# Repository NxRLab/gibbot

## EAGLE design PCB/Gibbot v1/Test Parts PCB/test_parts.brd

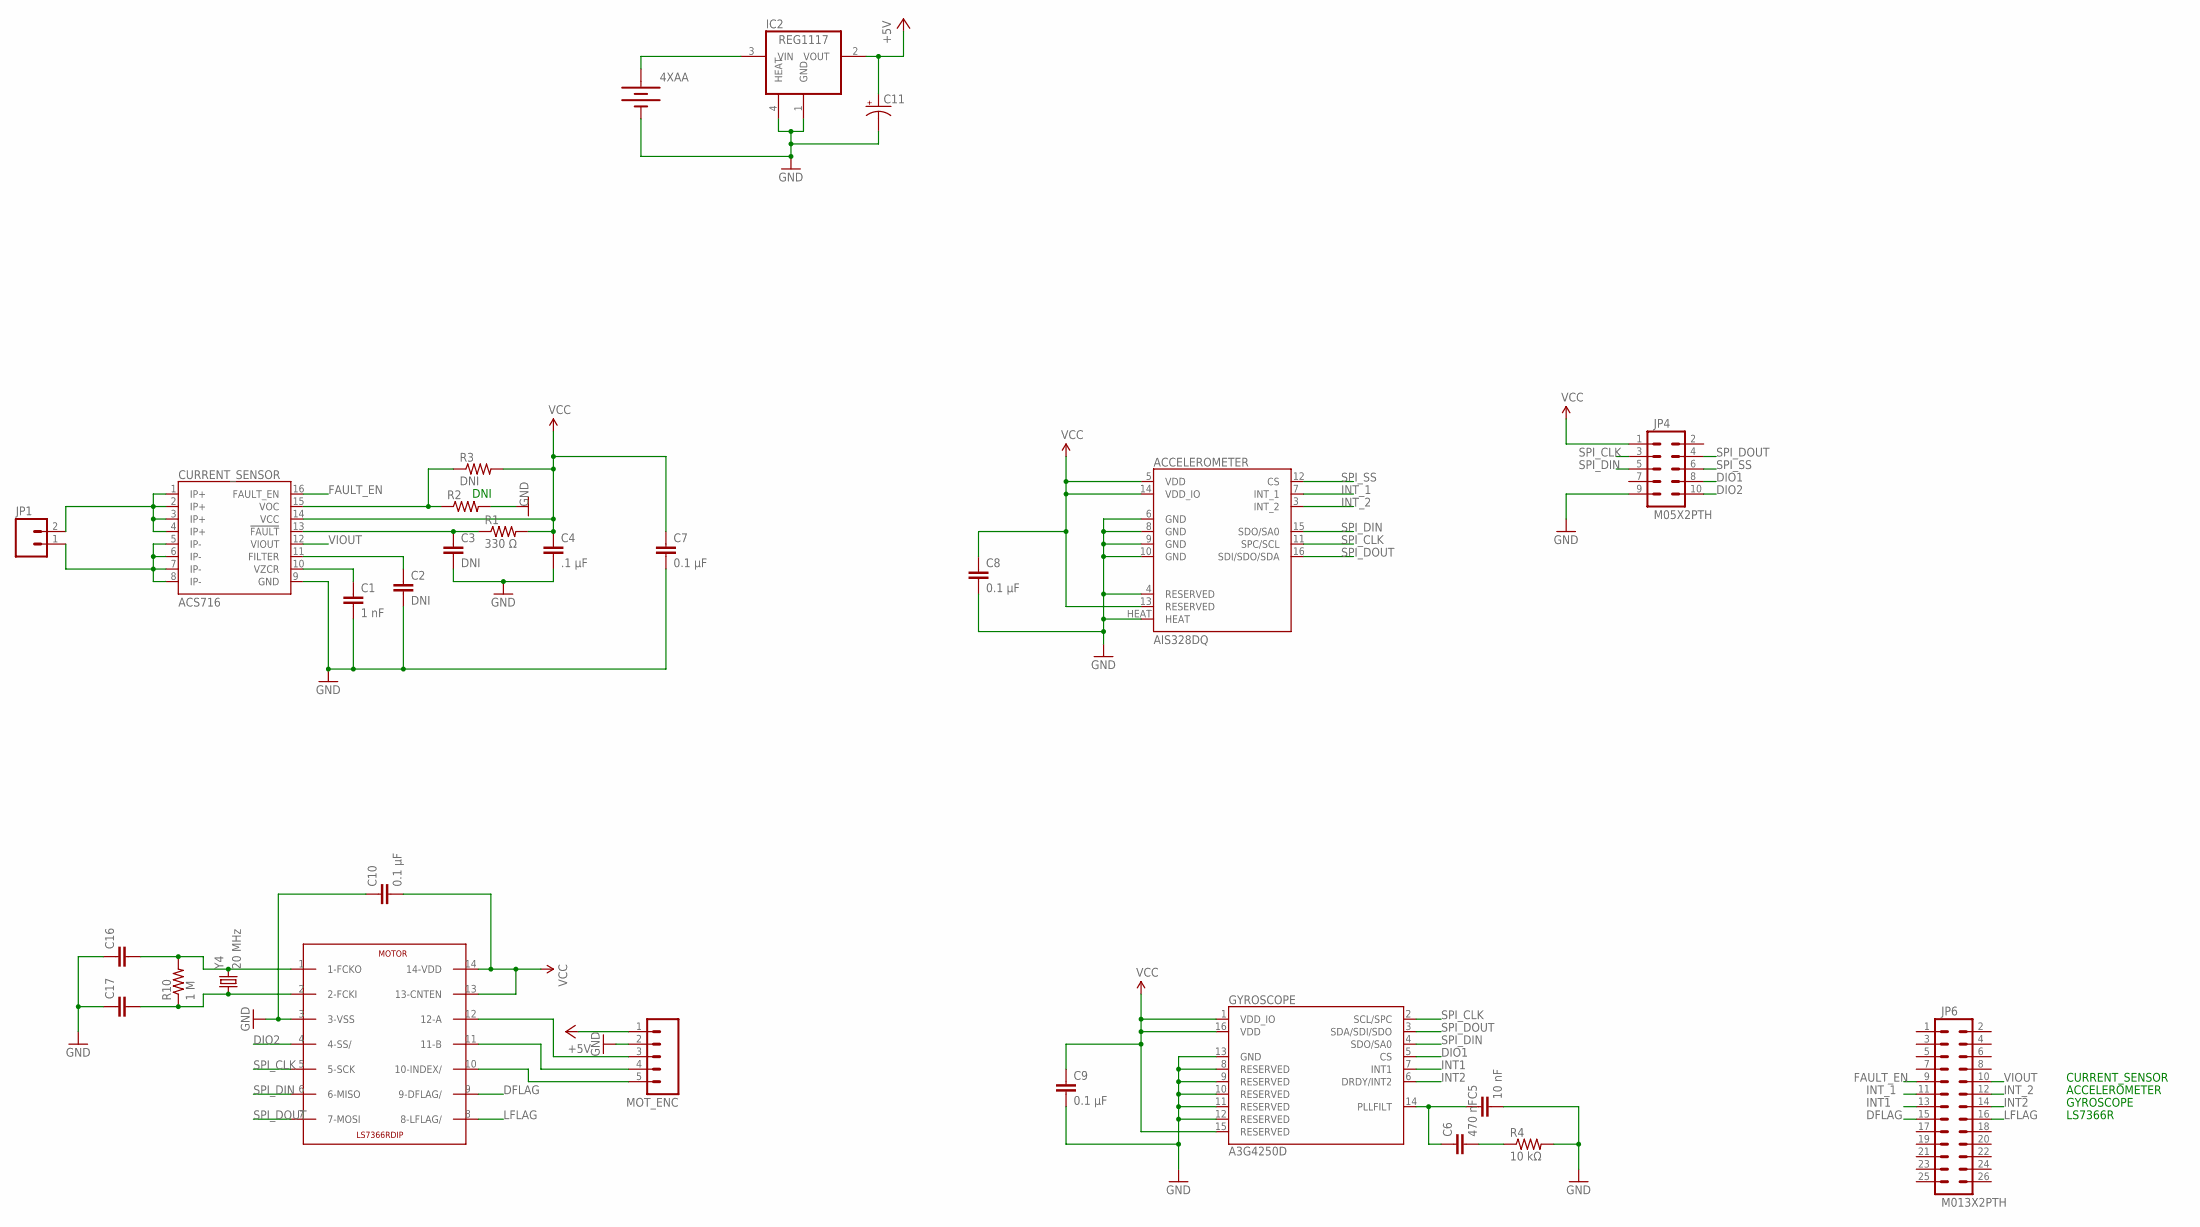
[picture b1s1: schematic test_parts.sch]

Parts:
4XAA: BATTERYTOP; BH4AA-PC
ACCELEROMETER: AIS328DQ; QFPN-24
C1: 1 nF; 0603-CAP
C2, C3: DNI; 0603-CAP
C4: .1 µF; 0603-CAP
C5: 10 nF; 0603-CAP
C6: 470 nF; 0603-CAP
C7, C8, C9, C10: 0.1 µF; 0603-CAP
C11: CAP_POL0603; 0603-CAP
C16, C17: CAP0603-CAP; 0603-CAP
CURRENT_SENSOR: ACS716; SOICW
GYROSCOPE: A3G4250D; LGA-16
IC2: REG1117; SOT223
JP1: M02PTH; 1X02
JP4: M05X2PTH; AVR_ICSP
JP6: M013X2PTH; AVR_ICSP
MOTOR: LS7366RDIP; DIL14
MOT_ENC: M05PTH; 1X05
R1: 330 Ω; 0603-RES
R2, R3: DNI; 0603-RES
R4: 10 kΩ; 0603-RES
R10: 1 M; R0603
Y4: 20 MHz; HC49US

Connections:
+5V: C11.1 (+), IC2.2 (VOUT), MOT_ENC.1
DFLAG: JP6.15, MOTOR.9 (9-DFLAG/)
DIO1: GYROSCOPE.5 (CS), JP4.8
DIO2: JP4.10, MOTOR.4 (4-SS/)
FAULT_EN: CURRENT_SENSOR.16 (FAULT_EN), JP6.9
GND: 4XAA.-, ACCELEROMETER.4 (RESERVED), ACCELEROMETER.6 (GND), ACCELEROMETER.8 (GND), ACCELEROMETER.9 (GND), ACCELEROMETER.10 (GND), ACCELEROMETER.HEAT, C1.2, C2.2, C3.2, C4.2, C5.2, C7.2, C8.2, C9.2, C10.1, C11.2 (-), C16.1, C17.1, CURRENT_SENSOR.9 (GND), GYROSCOPE.8 (RESERVED), GYROSCOPE.9 (RESERVED), GYROSCOPE.10 (RESERVED), GYROSCOPE.11 (RESERVED), GYROSCOPE.12 (RESERVED), GYROSCOPE.13 (GND), IC2.1 (GND), IC2.4 (HEAT), JP4.9, MOTOR.3 (3-VSS), MOT_ENC.2, R2.2, R4.2
INT1: GYROSCOPE.7 (INT1), JP6.13
INT2: GYROSCOPE.6 (DRDY/INT2), JP6.14
INT_1: ACCELEROMETER.7 (INT_1), JP6.11
INT_2: ACCELEROMETER.3 (INT_2), JP6.12
LFLAG: JP6.16, MOTOR.8 (8-LFLAG/)
unnamed: CURRENT_SENSOR.1 (IP+), CURRENT_SENSOR.2 (IP+), CURRENT_SENSOR.3 (IP+), CURRENT_SENSOR.4 (IP+), JP1.2
unnamed: CURRENT_SENSOR.5 (IP-), CURRENT_SENSOR.6 (IP-), CURRENT_SENSOR.7 (IP-), CURRENT_SENSOR.8 (IP-), JP1.1
unnamed: C3.1, CURRENT_SENSOR.13 (!FAULT), R1.1
unnamed: C1.1, CURRENT_SENSOR.10 (VZCR)
unnamed: C2.1, CURRENT_SENSOR.11 (FILTER)
unnamed: 4XAA.+, IC2.3 (VIN)
unnamed: CURRENT_SENSOR.15 (VOC), R2.1, R3.1
unnamed: C5.1, C6.1, GYROSCOPE.14 (PLLFILT)
unnamed: C6.2, R4.1
unnamed: C16.2, MOTOR.1 (1-FCKO), R10.2, Y4.2
unnamed: C17.2, MOTOR.2 (2-FCKI), R10.1, Y4.1
unnamed: MOTOR.12 (12-A), MOT_ENC.3
unnamed: MOTOR.11 (11-B), MOT_ENC.4
unnamed: MOTOR.10 (10-INDEX/), MOT_ENC.5
SPI_CLK: ACCELEROMETER.11 (SPC/SCL), GYROSCOPE.2 (SCL/SPC), JP4.3, MOTOR.5 (5-SCK)
SPI_DIN: ACCELEROMETER.15 (SDO/SA0), GYROSCOPE.4 (SDO/SA0), JP4.5, MOTOR.6 (6-MISO)
SPI_DOUT: ACCELEROMETER.16 (SDI/SDO/SDA), GYROSCOPE.3 (SDA/SDI/SDO), JP4.4, MOTOR.7 (7-MOSI)
SPI_SS: ACCELEROMETER.12 (CS), JP4.6
VCC: ACCELEROMETER.5 (VDD), ACCELEROMETER.13 (RESERVED), ACCELEROMETER.14 (VDD_IO), C4.1, C7.1, C8.1, C9.1, C10.2, CURRENT_SENSOR.14 (VCC), GYROSCOPE.1 (VDD_IO), GYROSCOPE.15 (RESERVED), GYROSCOPE.16 (VDD), JP4.1, MOTOR.13 (13-CNTEN), MOTOR.14 (14-VDD), R1.2, R3.2
VIOUT: CURRENT_SENSOR.12 (VIOUT), JP6.10

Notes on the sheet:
CURRENT_SENSOR
ACCELEROMETER
GYROSCOPE
LS7366R

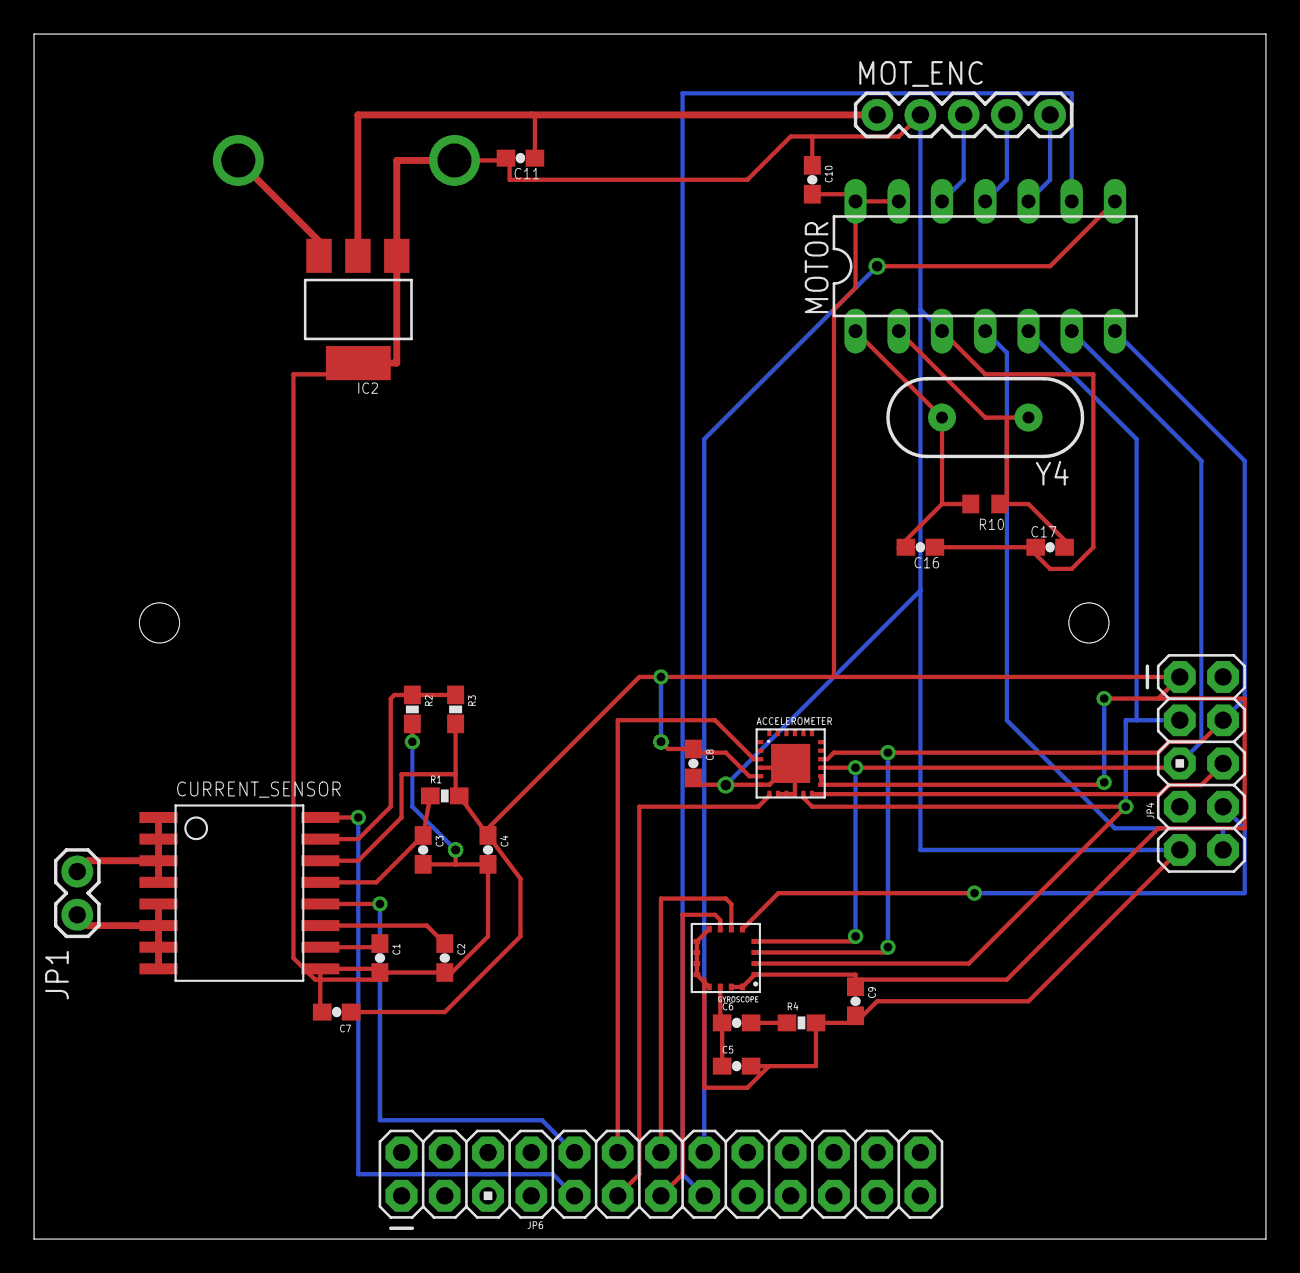
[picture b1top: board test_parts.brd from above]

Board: 2 copper layers, 72.4 x 70.8 mm, 29 parts (1 on the bottom side), 31 nets.

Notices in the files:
parts and their libraries:
SparkFun: Licensing: CC v3.0 Share-Alike You are welcome to use this library for commercial purposes.
